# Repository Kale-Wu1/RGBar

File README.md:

# RGBar
RGBoard is an 8 key macropad with a rotary encoder. Each key is backlit with a SK6812 reverse mounted neopixel.

### Inspiration
I had some extra time, and wanted to make something sleek and minimalist...with RGB, of course ;)

### Challenges
This was my first PCB, so the routing took a while... hopefully it works - DRC looked pretty good!

## Features
- 3D printed case
- EC11 rotary encoder
- 8 keys w/ rgb backlighting

## CAD
The top and bottom are assembled using 4 M3 bolts and heated inserts. 

## PCB
The PCB was made in KiCad - the board is powered by a Seeed Studio XIAO RP2040.

Here's the schematic:

...and the PCB:

## Firmware
This hackpad uses KMK firmware. Currently, RGBar just acts like a numpad (with backlighting on press) and the rotary encoder adjusts screen brightness, but it can be reprogrammed to do much more...

## BOM
### Custom Components
- 1x Custom PCB
- 1x 3D printed case (top, bottom, and knob)
- 8x 3D printed keycaps (...or any other keycap for Cherry MX switches)
  
### COTS Components
- 8x Cherry MX switches (4 clicky and 4 linear as a personal preference~)
- 8x 1N4148 Diodes (through hole)
- 8x SK6812 MINI-E LEDs
- 1x EC11 Rotary encoder
- 1x Seeed XIAO RP2040 (through hole)
- 14x Male headers
- 4x M3 x 6mm Screws
- 4x M3x5mx4mm heatset inserts

## Extra stuff
I built this as a part of Hack Club's Hackpad program. I haven't tested any of it yet, since I don't currently have the parts~

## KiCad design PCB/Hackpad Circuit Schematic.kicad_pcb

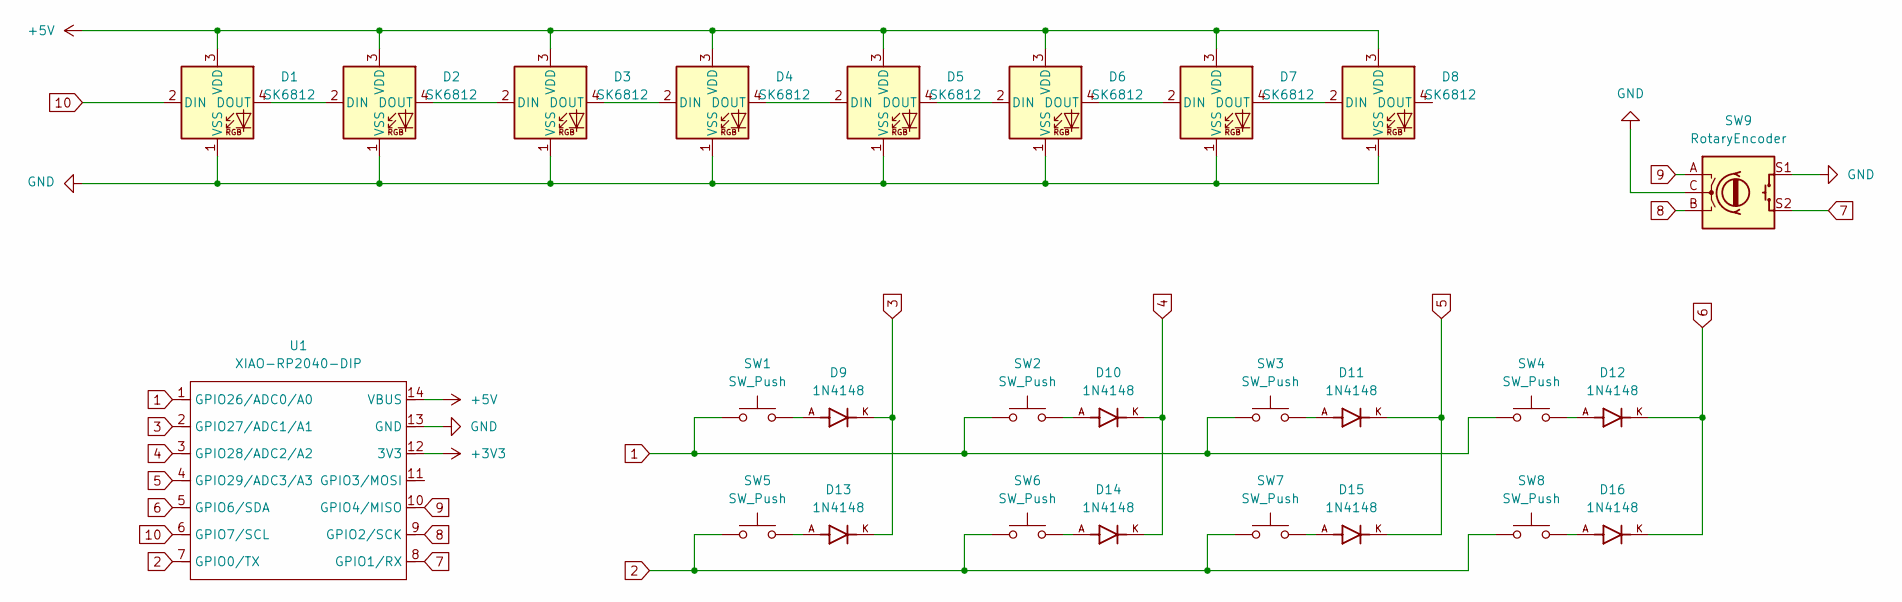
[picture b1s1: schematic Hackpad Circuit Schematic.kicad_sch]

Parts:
D1, D2, D3, D4, D5, D6, D7, D8: SK6812; MX-1U-SK6812Mini-E
D9, D10, D11, D12, D13, D14, D15, D16: 1N4148; DIOAD753W49L380D172B; PARTREV 5
SW1, SW2, SW3, SW4, SW5, SW6, SW7, SW8: SW_Push; SW_Cherry_MX_1.00u_PCB
SW9: RotaryEncoder; RotaryEncoder_Alps_EC11E-Switch_Vertical_H20mm_CircularMoun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
U1: XIAO-RP2040-DIP

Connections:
1: SW1.1, SW2.1, SW3.1, SW4.1, U1.1 (GPIO26/ADC0/A0)
2: SW5.1, SW6.1, SW7.1, SW8.1, U1.7 (GPIO0/TX)
3: D9.K, D13.K, U1.2 (GPIO27/ADC1/A1)
4: D10.K, D14.K, U1.3 (GPIO28/ADC2/A2)
5: D11.K, D15.K, U1.4 (GPIO29/ADC3/A3)
6: D12.K, D16.K, U1.5 (GPIO6/SDA)
7: SW9.S2, U1.8 (GPIO1/RX)
8: SW9.B, U1.9 (GPIO2/SCK)
9: SW9.A, U1.10 (GPIO4/MISO)
10: D1.2 (DIN), U1.6 (GPIO7/SCL)
+3V3: U1.12 (3V3)
+5V: D1.3 (VDD), D2.3 (VDD), D3.3 (VDD), D4.3 (VDD), D5.3 (VDD), D6.3 (VDD), D7.3 (VDD), D8.3 (VDD), U1.14 (VBUS)
GND: D1.1 (VSS), D2.1 (VSS), D3.1 (VSS), D4.1 (VSS), D5.1 (VSS), D6.1 (VSS), D7.1 (VSS), D8.1 (VSS), SW9.C, SW9.S1, U1.13 (GND)
unnamed: D1.4 (DOUT), D2.2 (DIN)
unnamed: D2.4 (DOUT), D3.2 (DIN)
unnamed: D3.4 (DOUT), D4.2 (DIN)
unnamed: D4.4 (DOUT), D5.2 (DIN)
unnamed: D5.4 (DOUT), D6.2 (DIN)
unnamed: D6.4 (DOUT), D7.2 (DIN)
unnamed: D7.4 (DOUT), D8.2 (DIN)
unnamed: D9.A, SW1.2
unnamed: D10.A, SW2.2
unnamed: D11.A, SW3.2
unnamed: D12.A, SW4.2
unnamed: D13.A, SW5.2
unnamed: D14.A, SW6.2
unnamed: D15.A, SW7.2
unnamed: D16.A, SW8.2

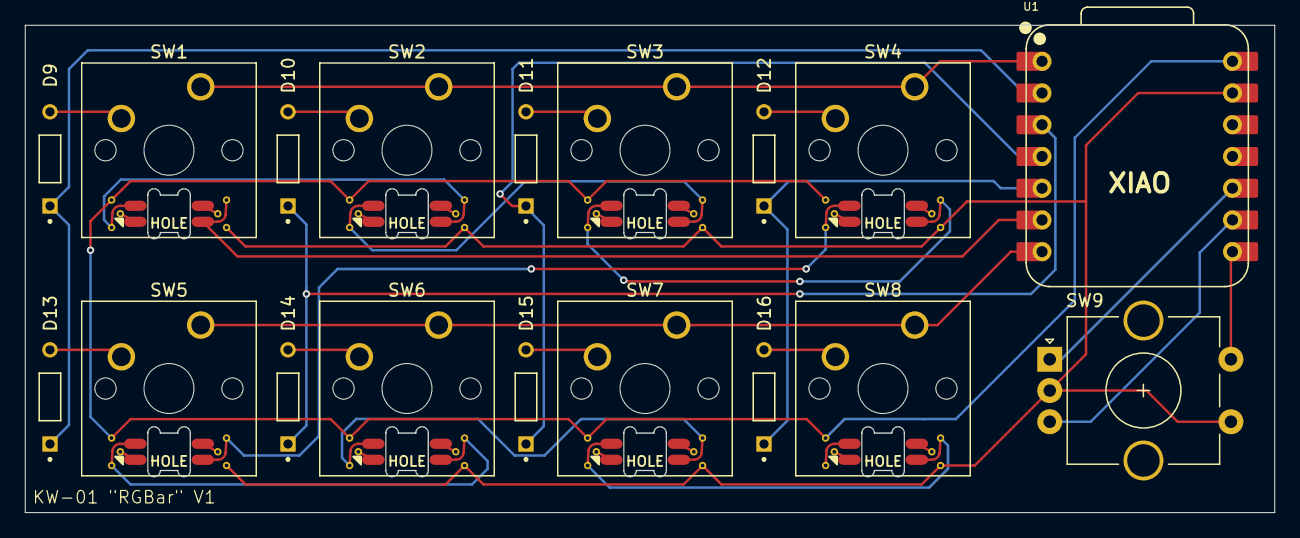
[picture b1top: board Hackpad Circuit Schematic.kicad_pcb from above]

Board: 2 copper layers, 100.0 x 39.0 mm, 26 parts (0 on the bottom side), 27 nets.

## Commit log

2025-02-20 Initial commit
    From local files to github
2025-02-20 Move files to KMK
2025-02-20 Rename
2025-02-20 Remove extra files
    Backup files and options.json
